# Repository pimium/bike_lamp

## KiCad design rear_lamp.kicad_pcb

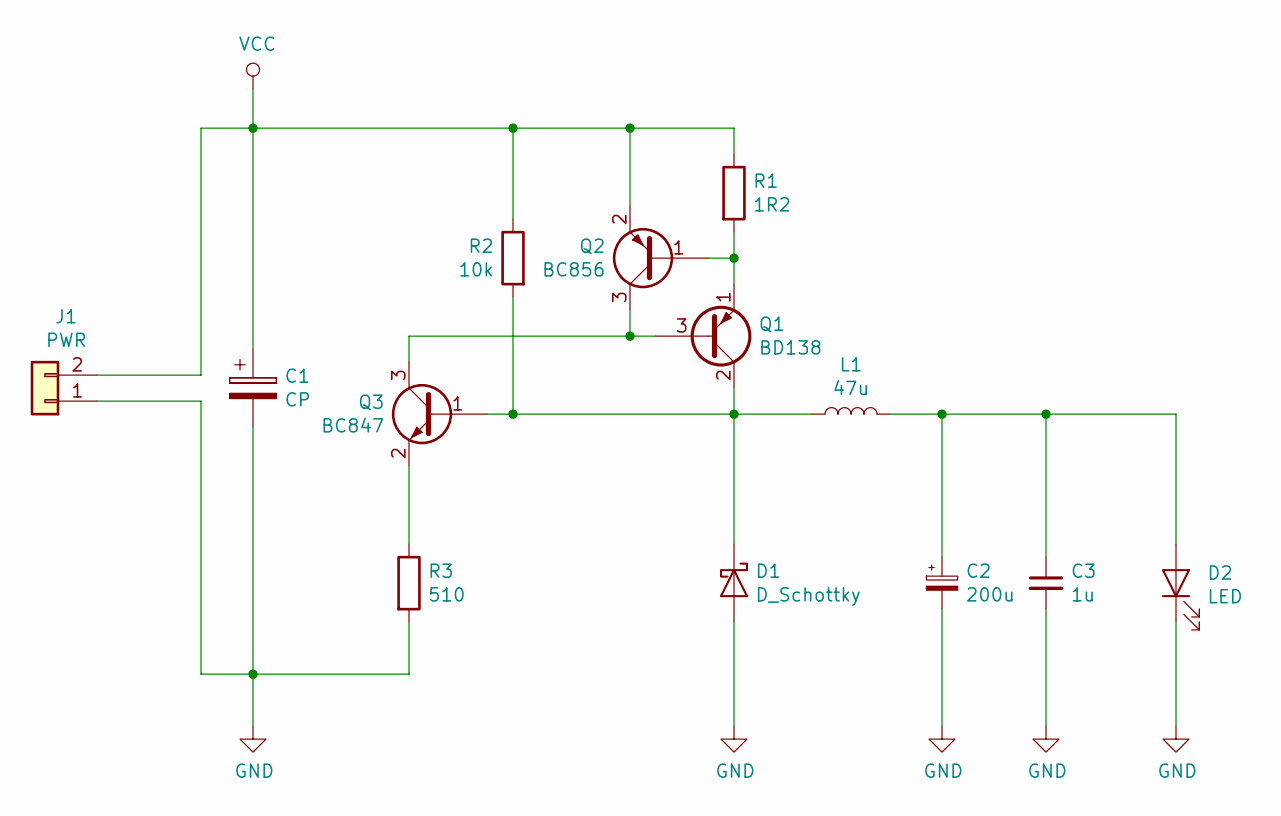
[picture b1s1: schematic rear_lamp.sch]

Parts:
C1: CP; C_Axial_L5.1mm_D3.1mm_P12.50mm_Horizontal
C2: 200u; CP_Radial_D8.0mm_P3.80mm
C3: 1u; C_0805_2012Metric_Pad1.15x1.40mm_HandSolder
D1: D_Schottky; D_SMA_Handsoldering
D2: LED; C_Axial_L5.1mm_D3.1mm_P12.50mm_Horizontal
J1: PWR; SolderWirePad_1x02_P3.81mm_Drill1mm
L1: 47u; L_Bourns_SRP7028A_7.3x6.6mm
Q1: BD138; TO-126-3_Vertical
Q2: BC856; SOT-23
Q3: BC847; SOT-23
R1: 1R2; R_1206_3216Metric_Pad1.42x1.75mm_HandSolder
R2: 10k; R_0805_2012Metric_Pad1.15x1.40mm_HandSolder
R3: 510; R_0805_2012Metric_Pad1.15x1.40mm_HandSolder

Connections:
GND: C1.2, C2.2, C3.2, D1.2 (A), D2.1 (K), J1.1, R3.2
unnamed: C2.1, C3.1, D2.2 (A), L1.2
unnamed: D1.1 (K), L1.1, Q1.2 (C), Q3.1 (B), R2.2
unnamed: Q1.1 (E), Q2.1 (B), R1.2
unnamed: Q1.3 (B), Q2.3 (C), Q3.3 (C)
unnamed: Q3.2 (E), R3.1
VCC: C1.1, J1.2, Q2.2 (E), R1.1, R2.1

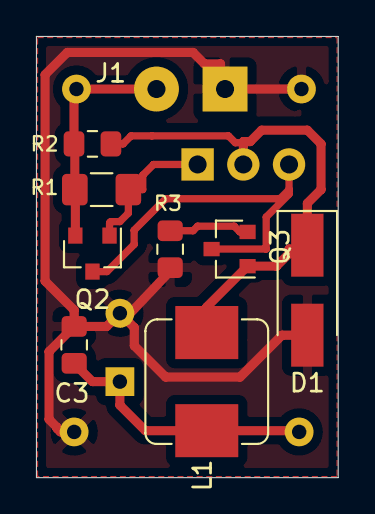
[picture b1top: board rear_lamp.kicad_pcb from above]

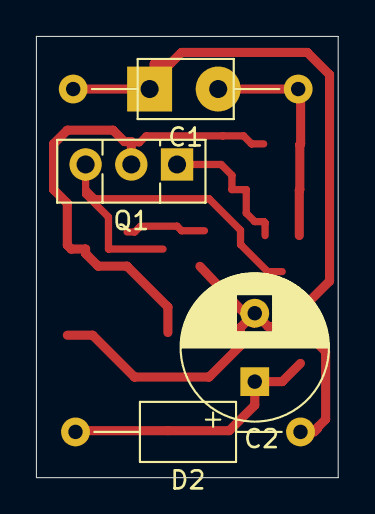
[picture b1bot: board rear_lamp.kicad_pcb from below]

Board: 2 copper layers, 16.8 x 24.5 mm, 13 parts (4 on the bottom side), 7 nets.

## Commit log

2024-03-18 just a current sink
2024-03-20 discrete led driver
2024-03-25 one plane
2024-03-25 small pcb
